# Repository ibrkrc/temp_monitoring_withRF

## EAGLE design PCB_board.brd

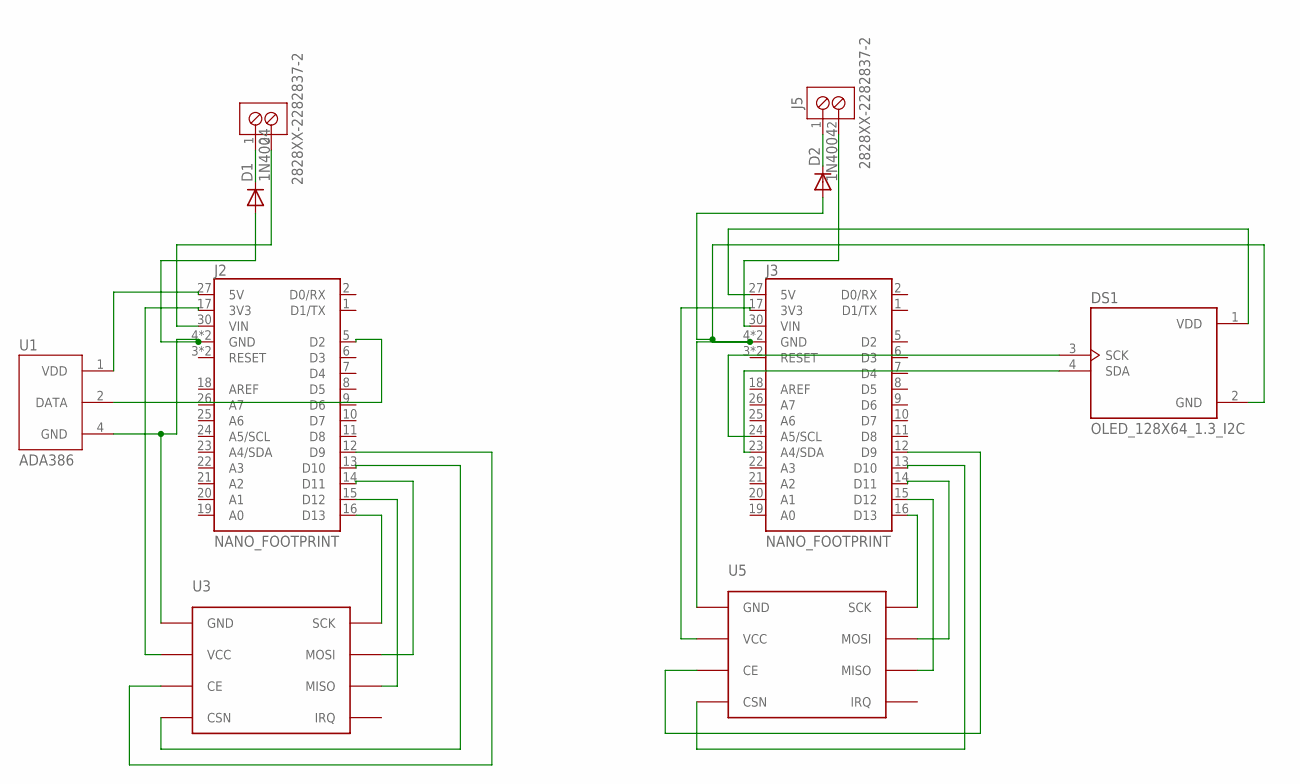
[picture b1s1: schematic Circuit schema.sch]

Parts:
D1, D2: 1N4004; DO41-10
DS1: OLED_128X64_1.3_I2C; LCD_OLED_128X64_1.3_I2C
J2, J3: NANO_FOOTPRINT; NANO
J4, J5: 2828XX-2282837-2; TERMBLK_508-2N
U1: ADA386; XDCR_ADA386
U3, U5: NRF24L01+-PCB-AERIAL; NRF24L01-PCB-AERIAL

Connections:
unnamed: D1.A, J2.4 (GND), J2.29 (GND), U1.4 (GND), U3.P$1 (GND)
unnamed: J2.5 (D2), U1.2 (DATA)
unnamed: J2.17 (3V3), U3.P$2 (VCC)
unnamed: J2.12 (D9), U3.P$3 (CE)
unnamed: J2.13 (D10), U3.P$4 (CSN)
unnamed: J2.16 (D13), U3.P$5 (SCK)
unnamed: J2.14 (D11), U3.P$6 (MOSI)
unnamed: J2.15 (D12), U3.P$7 (MISO)
unnamed: D2.A, DS1.2 (GND), J3.4 (GND), J3.29 (GND), U5.P$1 (GND)
unnamed: DS1.1 (VDD), J3.27 (5V)
unnamed: J3.17 (3V3), U5.P$2 (VCC)
unnamed: J3.12 (D9), U5.P$3 (CE)
unnamed: J3.13 (D10), U5.P$4 (CSN)
unnamed: J3.16 (D13), U5.P$5 (SCK)
unnamed: J3.14 (D11), U5.P$6 (MOSI)
unnamed: J3.15 (D12), U5.P$7 (MISO)
unnamed: DS1.3 (SCK), J3.24 (A5/SCL)
unnamed: DS1.4 (SDA), J3.23 (A4/SDA)
unnamed: J2.27 (5V), U1.1 (VDD)
unnamed: D1.C, J4.1
unnamed: J2.30 (VIN), J4.2
unnamed: D2.C, J5.1
unnamed: J3.30 (VIN), J5.2

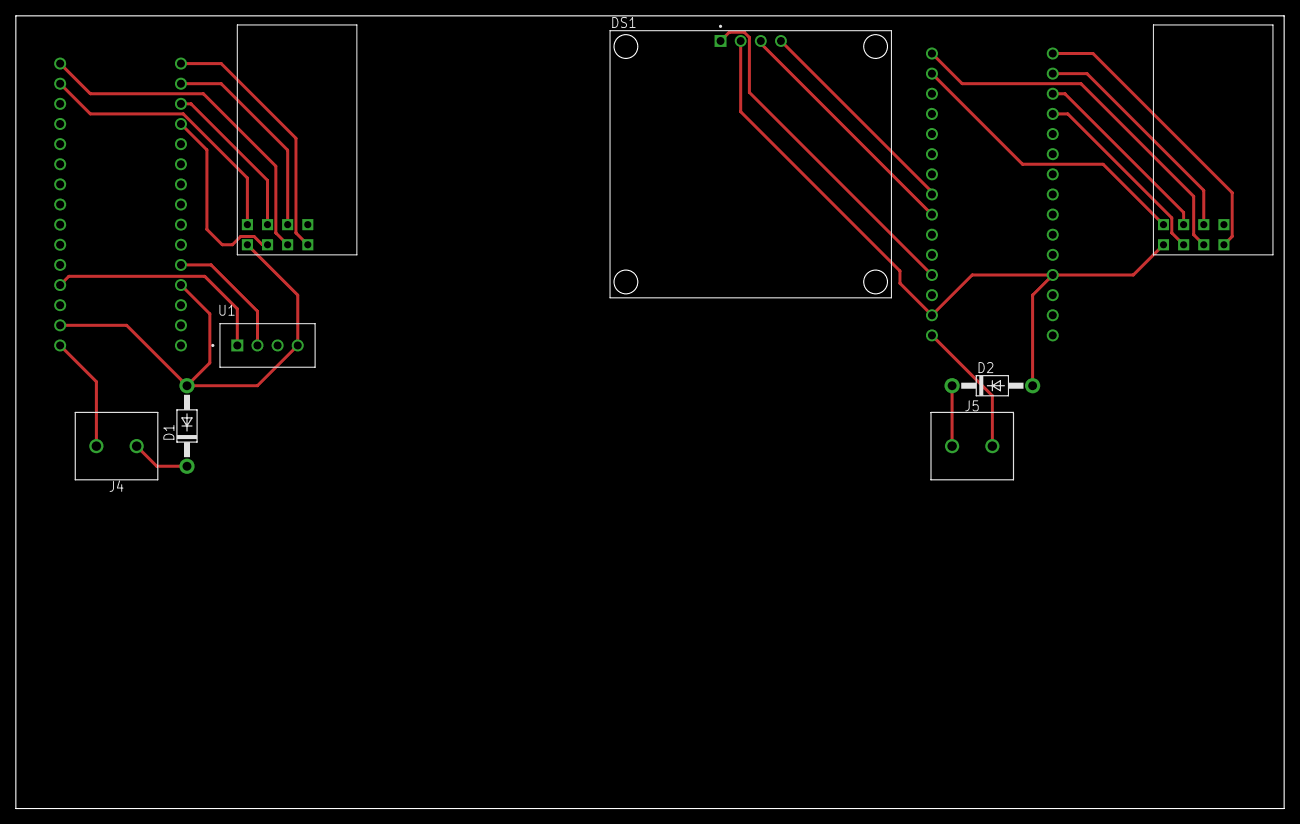
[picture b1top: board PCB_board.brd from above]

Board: 2 copper layers, 160.0 x 100.0 mm, 10 parts (0 on the bottom side), 23 nets.

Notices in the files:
parts and their libraries:
SparkFun-Boards: Licensing: Creative Commons ShareAlike 4.0 International - https://creativecommons.org/licenses/by-sa/4.0
